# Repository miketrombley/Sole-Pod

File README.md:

# Sole Pod Control System

An ESP32-based firmware for controlling a smart pod system with motorized door and tray, LED lighting, and wireless connectivity.

## 🚀 Features

### Core Functionality
- **Motorized Door & Tray Control**: Automated opening/closing sequence with precise position control
- **Smart LED Lighting**: Full-color NeoPixel LED with adjustable brightness and color
- **Hall Sensor Feedback**: Precise position detection for door and tray states
- **Safety Systems**: Motor stall detection with automatic shutdown
- **Persistent Settings**: All configurations saved to flash memory

### Connectivity
- **Bluetooth Low Energy (BLE)**: Local device control via mobile app
- **WiFi Integration**: Network connectivity with credential management
- **AWS IoT Core**: Cloud connectivity for remote monitoring and control
- **MQTT Communication**: Real-time state updates and commands

### User Interface
- **Physical Buttons**: Manual door and LED control
- **Child Lock**: Safety feature to prevent accidental operation
- **Status Indicators**: Real-time feedback on device state

## 📋 Hardware Requirements

### Compatible Hardware
- **Control Board**: v1.4
- **LED Board**: v1.2  
- **Hall Sensor Board**: v1.0
- **Microcontroller**: ESP32

### Pin Configuration
```cpp
// Motor Control
#define DOOR_MOTOR 46          // Door motor control
#define DOOR_DIRECTION 3       // Door motor direction
#define TRAY_MOTOR 10          // Tray motor control  
#define TRAY_DIRECTION 11      // Tray motor direction

// Sensors
#define SW_DOOR_CLOSED 45      // Door closed sensor
#define SW_DOOR_OPENED 48      // Door opened sensor
#define SW_TRAY_CLOSED 35      // Tray closed sensor
#define SW_TRAY_OPENED 36      // Tray opened sensor

// User Interface
#define DOOR_BTN 47            // Door control button
#define LED_BTN 21             // LED control button
#define LED_DATA_PIN 14        // NeoPixel data pin

// Safety
#define VOLTAGE_PIN 9          // Motor current monitoring
```

## 🏗️ Architecture

### System States
The pod operates in 5 distinct states:
1. **CLOSED** (0): Door closed, tray closed
2. **DOOR_MIDWAY** (1): Door transitioning, tray closed  
3. **DOOR_OPEN** (2): Door open, tray closed
4. **TRAY_MIDWAY** (3): Door open, tray transitioning
5. **OPEN** (4): Door open, tray open

### Operation Sequence
**Opening**: CLOSED → DOOR_MIDWAY → DOOR_OPEN → TRAY_MIDWAY → OPEN
**Closing**: OPEN → TRAY_MIDWAY → DOOR_OPEN → DOOR_MIDWAY → CLOSED

## 📱 BLE Interface

### Service UUID
`7d840001-11eb-4c13-89f2-246b6e0b0000`

### Characteristics
| Function | UUID | Type | Range | Description |
|----------|------|------|-------|-------------|
| Door Status | `7d840002-...0001` | R/W | 0-1 | 0=Closed, 1=Open |
| Door Position | `7d840003-...0002` | R/W | 50,100 | Partial/Full open |
| LED Status | `7d840004-...0003` | R/W | 0-1 | 0=Off, 1=On |
| LED Brightness | `7d840005-...0004` | R/W | 0-100 | Brightness percentage |
| LED Color | `7d840006-...0005` | R/W | Hex | 6-digit hex color code |
| WiFi Credentials | `7d840007-...0006` | W | String | Format: `SSIDENDNETWORKPASSWORDENDPASSWORD` |
| WiFi Status | `7d840008-...0007` | R/N | String | Connection status |

## ☁️ AWS IoT Integration

### Device Shadow Topics
- **Publish**: `$aws/things/pod_1/shadow/update`
- **Subscribe**: `$aws/things/pod_1/shadow/update/accepted`

### Shadow Document Structure
```json
{
  "state": {
    "reported": {
      "is_open": true,
      "nightlight": false,
      "color": "FF0000",
      "nightlight_brightness": 75
    },
    "desired": {
      "is_open": false,
      "nightlight": true,
      "color": "0000FF",
      "nightlight_brightness": 50
    }
  }
}
```

## 🔧 Configuration

### AWS Configuration
Update `aws_config.h` with your AWS IoT settings:
```cpp
#define AWS_IOT_ENDPOINT "your-endpoint-ats.iot.region.amazonaws.com"
#define DEVICE_NAME "your_device_name"
```

Replace the certificate and key constants with your device-specific credentials.

### WiFi Configuration
Default credentials can be set in `main.cpp`:
```cpp
const char* defaultSSID = "your_network";
const char* defaultPassword = "your_password";
```

## 🛡️ Safety Features

### Motor Stall Detection
- **Threshold**: 0.2V (configurable in `VoltageReader.h`)
- **Sampling**: 50-sample average for noise reduction
- **Response**: Immediate motor shutdown and system lockout
- **Recovery**: Requires power cycle after stall detection

### Child Lock
- Prevents accidental button operation
- Configurable via software flag
- Applies to both door and LED controls

## 📊 Debug Output

Enable debug mode in `main.cpp`:
```cpp
#define DEBUG_MODE true
```

### Debug Information Includes:
- Current pod state and target
- Sensor readings (door/tray positions)
- LED status (state, brightness, color)
- WiFi connection status and signal strength
- Motor voltage readings
- Safety system status

## 🔄 State Persistence

The system automatically saves and restores:
- LED color and brightness settings
- Door position preference (50% or 100% open)
- LED on/off state
- Door open/closed status

Settings are stored in ESP32 flash memory using the Preferences library.

## 🚦 Status Codes

### Safety Status
- `0`: OK - Normal operation
- `1`: Motor stall detected
- `2`: Obstacle detected  
- `3`: Overcurrent condition
- `4`: System error

### WiFi Status
- "Connected" - Successfully connected
- "Disconnected" - Not connected
- "Connection failed" - Failed to connect
- "SSID not available" - Network not found

## 🛠️ Development

### Dependencies
- Arduino ESP32 Core
- WiFiClientSecure
- PubSubClient (MQTT)
- ArduinoJson
- Adafruit NeoPixel
- ESP32 BLE Arduino
- Preferences

### Building
1. Install ESP32 board package in Arduino IDE
2. Install required libraries
3. Configure AWS certificates in `aws_config.h`
4. Upload to ESP32 device

### Testing
- Use serial monitor at 115200 baud for debug output
- Test BLE connectivity with compatible mobile app
- Verify AWS IoT connection in AWS Console
- Test all physical controls and sensors

## 📝 License

TBD

## 🤝 Contributing

[Add contribution guidelines if applicable]

## 📞 Support

[Add support contact information]

---

**Hardware Compatibility**: Control Board v1.4, LED Board v1.2, Hall Sensor Board v1.0

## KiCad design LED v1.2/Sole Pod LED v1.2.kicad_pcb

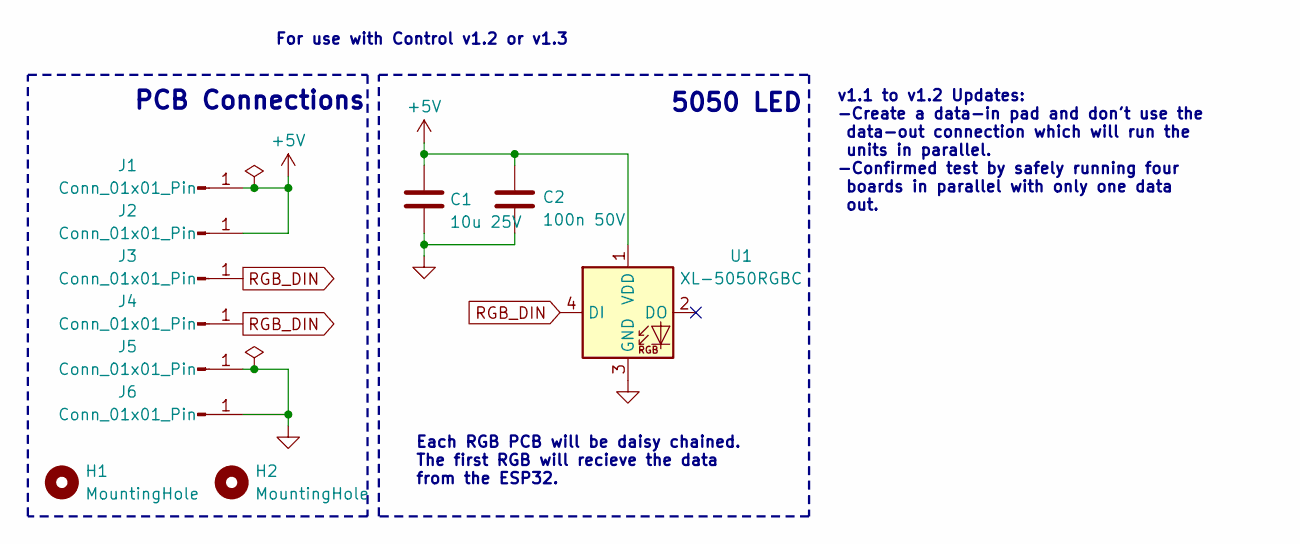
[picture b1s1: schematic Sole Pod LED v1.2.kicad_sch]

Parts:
C1: 10u 25V; C603; JLCPCB P/N C96446
C2: 100n 50V; C603; JLCPCB P/N C14663
H1, H2: MountingHole; MountingHole_2.5mm; JLCPCB P/N DNP
J1, J2, J3, J4, J5, J6: Conn_01x01_Pin; SolderWirePad_1x01_SMD_1x2mm; JLCPCB P/N DNP
U1: XL-5050RGBC; LED_Inolux_IN-PI554FCH_PLCC4_5.0x5.0mm_P3.2mm; JLCPCB P/N C2843785

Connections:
+5V: C1.1, C2.1, J1.1, J2.1, U1.1 (VDD)
GND: C1.2, C2.2, J5.1, J6.1, U1.3 (GND)
RGB_DIN: J3.1, J4.1, U1.4 (DI)

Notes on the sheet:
v1.1 to v1.2 Updates: -Create a data-in pad and don't use the data-out connection which will run the units in parallel. -Confirmed test by safely running four boards in parallel with only one data out.
PCB Connections
Each RGB PCB will be daisy chained. The first RGB will recieve the data from the ESP32.
5050 LED
For use with Control v1.2 or v1.3

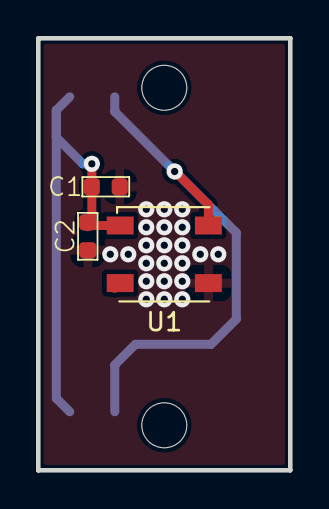
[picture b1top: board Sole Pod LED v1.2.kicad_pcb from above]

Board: 2 copper layers, 14.0 x 24.0 mm, 11 parts (0 on the bottom side), 3 nets.

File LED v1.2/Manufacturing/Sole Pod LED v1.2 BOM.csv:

Designator,Footprint,Quantity,Value,LCSC Part #
C1,C603,1,10u 25V,C96446
C2,C603,1,100n 50V,C14663
"J1, J2, J3, J4, J5, J6",SolderWirePad_1x01_SMD_1x2mm,6,Conn_01x01_Pin,DNP
U1,LED_Inolux_IN-PI554FCH_PLCC4_5.0x5.0mm_P3.2mm,1,XL-5050RGBC,C2843785

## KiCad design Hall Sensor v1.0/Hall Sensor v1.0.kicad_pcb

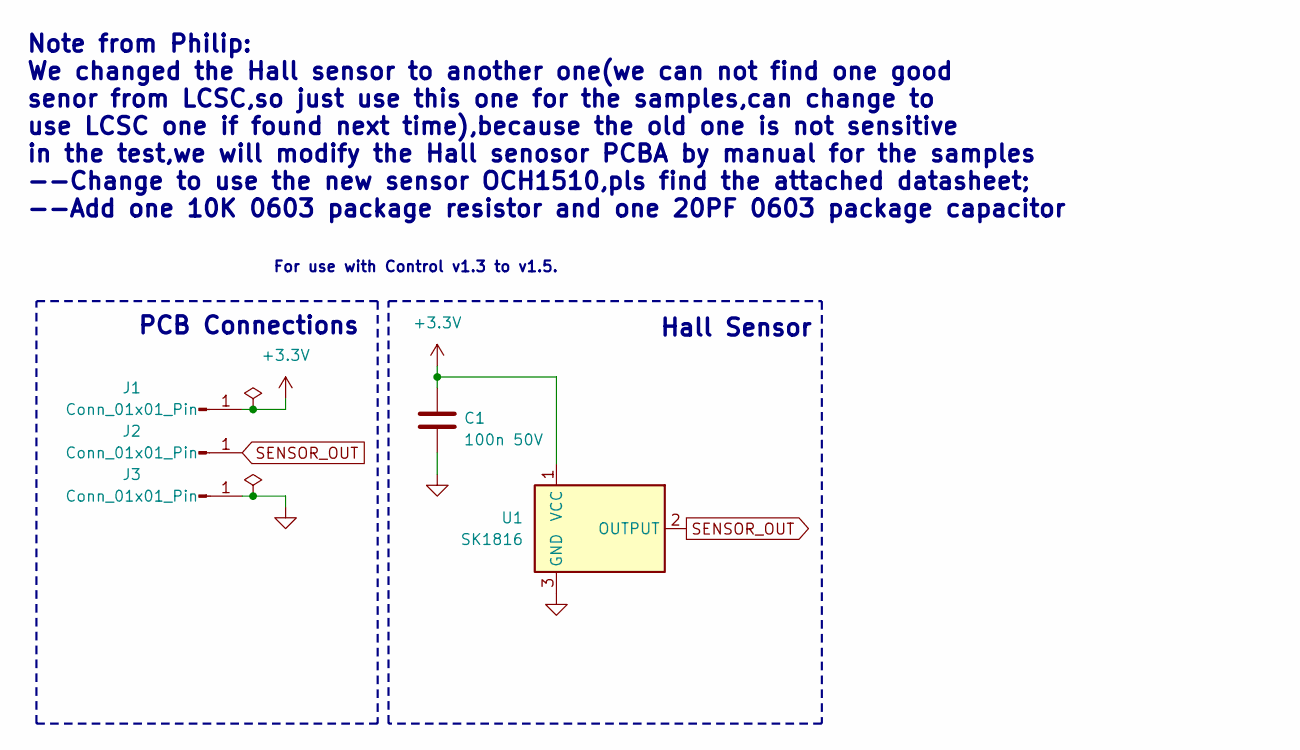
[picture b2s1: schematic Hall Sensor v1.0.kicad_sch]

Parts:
C1: 100n 50V; C603; JLCPCB P/N C14663
J1, J2, J3: Conn_01x01_Pin; SolderWirePad_1x01_SMD_1x2mm; JLCPCB P/N DNP
U1: SK1816; SOT-23; JLCPCB P/N C75517

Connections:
+3.3V: C1.1, J1.1, U1.1 (VCC)
GND: C1.2, J3.1, U1.3 (GND)
SENSOR_OUT: J2.1, U1.2 (OUTPUT)

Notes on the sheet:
PCB Connections
Hall Sensor
Note from Philip: We changed the Hall sensor to another one(we can not find one good senor from LCSC,so just use this one for the samples,can change to use LCSC one if found next time),because the old one is not sensitive in the test,we will modify the Hall senosor PCBA by manual for the samples --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
For use with Control v1.3 to v1.5.

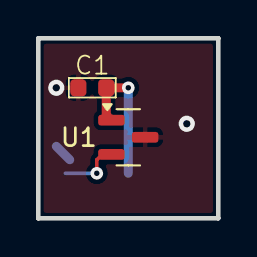
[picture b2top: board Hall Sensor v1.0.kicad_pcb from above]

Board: 2 copper layers, 10.0 x 10.0 mm, 5 parts (0 on the bottom side), 3 nets.

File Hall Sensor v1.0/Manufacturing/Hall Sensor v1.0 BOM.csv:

Designator,Footprint,Quantity,Value,LCSC Part #
C1,C603,1,100n 50V,C14663
"J1, J2, J3",SolderWirePad_1x01_SMD_1x2mm,3,Conn_01x01_Pin,DNP
U1,SOT-23,1,SK1816,C75517

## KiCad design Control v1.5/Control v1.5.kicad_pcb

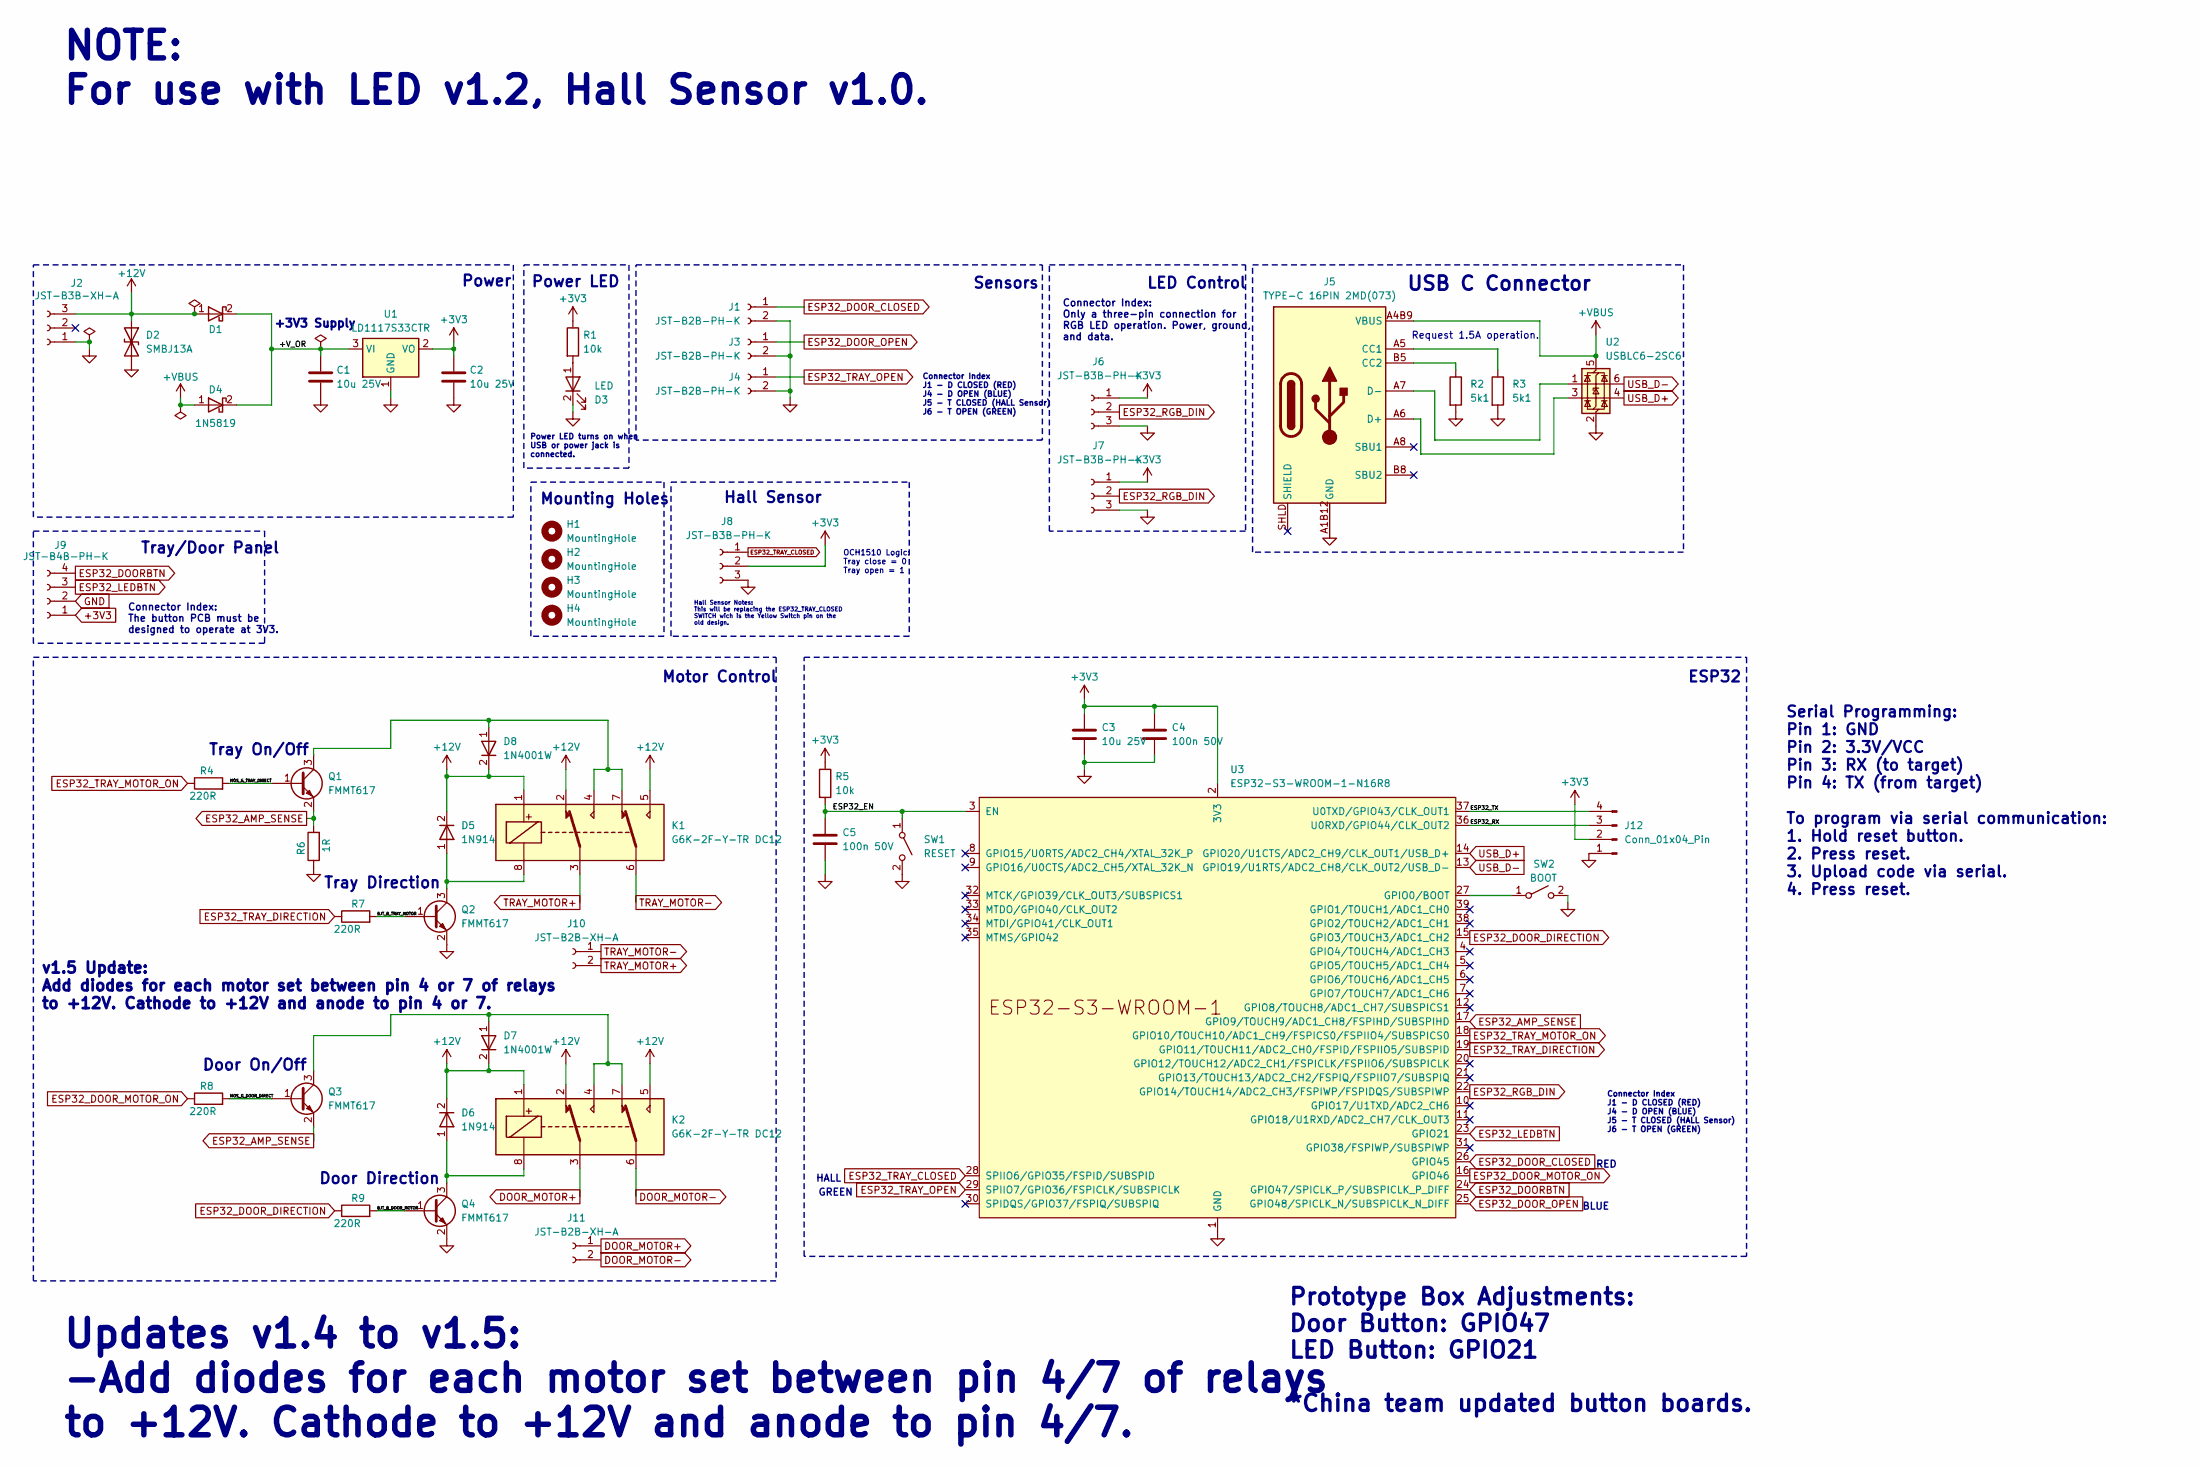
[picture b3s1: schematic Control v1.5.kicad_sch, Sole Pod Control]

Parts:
C1, C2, C3: 10u 25V; C603; LCSC Part # C96446
C4, C5: 100n 50V; C603; LCSC Part # C14663
D1, D4: 1N5819; D805; LCSC Part # C2927280
D2: SMBJ13A; D_SMB; LCSC Part # C152108
D3: LED; D603; LCSC Part # C497922
D5, D6: 1N914; D805; LCSC Part # C2128
D7, D8: 1N4001W; SOD-123; LCSC Part # C18199085
H1, H2, H3, H4: MountingHole; MountingHole_3mm; LCSC Part # DNP
J1, J3, J4: JST-B2B-PH-K; JST_PH_B2B-PH-K_1x02_P2.00mm_Vertical; LCSC Part # C131337
J2: JST-B3B-XH-A; JST_XH_B3B-XH-A_1x03_P2.50mm_Vertical; LCSC Part # C144394
J5: TYPE-C 16PIN 2MD(073); USB_C_TYPE-C_16PIN_2MD; LCSC Part # C2765186
J6, J7, J8: JST-B3B-PH-K; JST_PH_B3B-PH-K_1x03_P2.00mm_Vertical; LCSC Part # C131339
J9: JST-B4B-PH-K; JST_PH_B4B-PH-K_1x04_P2.00mm_Vertical; LCSC Part # C131334
J10, J11: JST-B2B-XH-A; JST_XH_B2B-XH-A_1x02_P2.50mm_Vertical; LCSC Part # C158012
J12: Conn_01x04_Pin; PinHeader_1x04_P2.54mm_Vertical; LCSC Part # C2691448
K1, K2: G6K-2F-Y-TR DC12; Relay_DPDT_Omron_G6K-2F-Y; LCSC Part # C397192
Q1, Q2, Q3, Q4: FMMT617; SOT-23-3; LCSC Part # C686650
R1, R5: 10k; R603; LCSC Part # C25804
R2, R3: 5k1; R603; LCSC Part # C25905
R4, R7, R8, R9: 220R; R603; LCSC Part # C22962
R6: 1R; R_1206_3216Metric; LCSC Part # C17928
SW1: RESET; SW_SPST_B3U-1000P; LCSC Part # C231329
SW2: BOOT; SW_SPST_B3U-1000P; LCSC Part # C231329
U1: LD1117S33CTR; SOT-223-3_TabPin2; LCSC Part # C35879
U2: USBLC6-2SC6; SOT-23-6; LCSC Part # C2827654
U3: ESP32-S3-WROOM-1-N16R8; ESP32-S3-WROOM-1; LCSC Part # C2913202

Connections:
+3V3: C2.1, C3.1, C4.1, J6.1, J7.1, J8.2, J9.1, J12.2, R1.1, R5.1, U1.2 (VO), U3.2 (3V3)
+12V: D1.1, D2.1 (A1), D5.2 (K), D6.2 (K), D7.2 (K), D8.2 (K), J2.3, K1.1, K1.2, K1.5, K2.1, K2.2, K2.5
+VBUS: D4.1, J5.A4B9 (VBUS), J5.B4A9 (VBUS), U2.5 (VBUS)
/+V_OR: C1.1, D1.2, D4.2, U1.3 (VI)
/BJT_B_DOOR_MOTOR: Q4.1 (B), R9.2
/BJT_B_TRAY_MOTOR: Q2.1 (B), R7.2
/ESP32_EN: C5.1, R5.2, SW1.1 (A), U3.3 (EN)
/ESP32_RX: J12.3, U3.36 (U0RXD/GPIO44/CLK_OUT2)
/ESP32_TX: J12.4, U3.37 (U0TXD/GPIO43/CLK_OUT1)
/MOS_G_DOOR_DIRECT: Q3.1 (B), R8.2
/MOS_G_TRAY_DIRECT: Q1.1 (B), R4.2
DOOR_MOTOR+: J11.1, K2.3
DOOR_MOTOR-: J11.2, K2.6
ESP32_AMP_SENSE: Q1.2 (E), Q3.2 (E), R6.2, U3.17 (GPIO9/TOUCH9/ADC1_CH8/FSPIHD/SUBSPIHD)
ESP32_DOORBTN: J9.4, U3.24 (GPIO47/SPICLK_P/SUBSPICLK_P_DIFF)
ESP32_DOOR_CLOSED: J1.1, U3.26 (GPIO45)
ESP32_DOOR_DIRECTION: R9.1, U3.15 (GPIO3/TOUCH3/ADC1_CH2)
ESP32_DOOR_MOTOR_ON: R8.1, U3.16 (GPIO46)
ESP32_DOOR_OPEN: J3.1, U3.25 (GPIO48/SPICLK_N/SUBSPICLK_N_DIFF)
ESP32_LEDBTN: J9.3, U3.23 (GPIO21)
ESP32_RGB_DIN: J6.2, J7.2, U3.22 (GPIO14/TOUCH14/ADC2_CH3/FSPIWP/FSPIDQS/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)
ESP32_TRAY_CLOSED: J8.1, U3.28 (SPIIO6/GPIO35/FSPID/SUBSPID)
ESP32_TRAY_DIRECTION: R7.1, U3.19 (GPIO11/TOUCH11/ADC2_CH0/FSPID/FSPIIO5/S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)
ESP32_TRAY_MOTOR_ON: R4.1, U3.18 (GPIO10/TOUCH10/ADC1_CH9/FSPICS0/FSPIIO4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)
ESP32_TRAY_OPEN: J4.1, U3.29 (SPIIO7/GPIO36/FSPICLK/SUBSPICLK)
GND: C1.2, C2.2, C3.2, C4.2, C5.2, D2.2 (A2), D3.2 (K), J1.2, J2.1, J3.2, J4.2, J5.A1B12 (GND), J5.B1A12 (GND), J6.3, J7.3, J8.3, J9.2, J12.1, Q2.2 (E), Q4.2 (E), R2.2, R3.2, R6.1, SW1.2 (B), SW2.2 (B), U1.1 (GND), U2.2 (GND), U3.1 (GND), U3.40 (GND), U3.41 (GND)
unnamed: D3.1 (A), R1.2
unnamed: D5.1 (A), K1.8, Q2.3 (C)
unnamed: D6.1 (A), K2.8, Q4.3 (C)
unnamed: D7.1 (A), K2.4, K2.7, Q3.3 (C)
unnamed: D8.1 (A), K1.4, K1.7, Q1.3 (C)
unnamed: J5.A5 (CC1), R3.1
unnamed: J5.B5 (CC2), R2.1
unnamed: J5.A6 (D+), J5.B6 (D+), U2.3 (I/O2)
unnamed: J5.A7 (D-), J5.B7 (D-), U2.1 (I/O1)
unnamed: SW2.1 (A), U3.27 (GPIO0/BOOT)
TRAY_MOTOR+: J10.2, K1.3
TRAY_MOTOR-: J10.1, K1.6
USB_D+: U2.4 (I/O2), U3.14 (GPIO20/U1CTS/ADC2_CH9/CLK_OUT1/USB_D+)
USB_D-: U2.6 (I/O1), U3.13 (GPIO19/U1RTS/ADC2_CH8/CLK_OUT2/USB_D-)

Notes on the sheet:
Tray On/Off
ESP32
HALL
NOTE: For use with LED v1.2, Hall Sensor v1.0.
USB C Connector
Connector Index: Only a three-pin connection for RGB LED operation. Power, ground, and data.
BLUE
Mounting Holes
Tray Direction
v1.5 Update: Add diodes for each motor set between pin 4 or 7 of relays to +12V. Cathode to +12V and anode to pin 4 or 7.
Connector Index J1 - D CLOSED (RED) J4 - D OPEN (BLUE) J5 - T CLOSED (HALL Sensor) J6 - T OPEN (GREEN)
Updates v1.4 to v1.5: -Add diodes for each motor set between pin 4/7 of relays to +12V. Cathode to +12V and anode to pin 4/7.
Connector Index: The button PCB must be designed to operate at 3V3.
Motor Control
Request 1.5A operation.
GREEN
OCH1510 Logic: Tray close = 0 Tray open = 1
Power LED
Sensors
Door Direction
Serial Programming: Pin 1: GND Pin 2: 3.3V/VCC Pin 3: RX (to target) Pin 4: TX (from target) To program via serial communication: 1. Hold reset button. 2. Press reset. 3. Upload code via serial. 4. Press reset.
Hall Sensor
Tray/Door Panel
Power LED turns on when USB or power jack is connected.
Hall Sensor Notes: This will be replacing the ESP32_TRAY_CLOSED SWITCH wich is the Yellow Switch pin on the old design.
Door On/Off
+3V3 Supply
Power
RED
Prototype Box Adjustments: Door Button: GPIO47 LED Button: GPIO21 *China team updated button boards.
LED Control

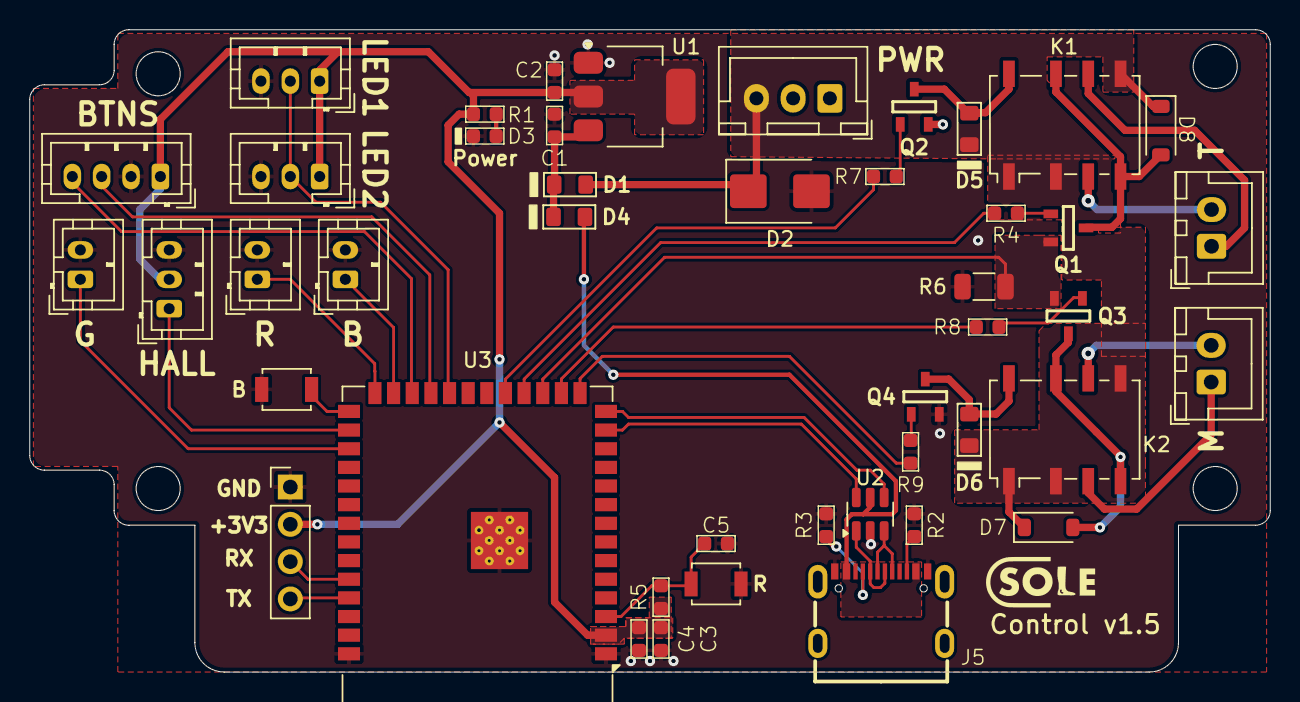
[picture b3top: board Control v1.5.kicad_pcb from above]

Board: 2 copper layers, 84.5 x 43.8 mm, 49 parts (0 on the bottom side), 40 nets.

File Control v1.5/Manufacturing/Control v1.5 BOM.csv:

Designator,Footprint,Quantity,Value,LCSC Part #
"C1, C2, C3",C603,3,10u 25V,C96446
"C4, C5",C603,2,100n 50V,C14663
"D1, D4",D805,2,1N5819,C2927280
D2,D_SMB,1,SMBJ13A,C152108
D3,D603,1,LED,C497922
"D5, D6",D805,2,1N914,C2128
"D7, D8",SOD-123,2,1N4001W,C18199085
"J1, J3, J4",JST_PH_B2B-PH-K_1x02_P2.00mm_Vertical,3,JST-B2B-PH-K,C131337
"J10, J11",JST_XH_B2B-XH-A_1x02_P2.50mm_Vertical,2,JST-B2B-XH-A,C158012
J12,PinHeader_1x04_P2.54mm_Vertical,1,Conn_01x04_Pin,C2691448
J2,JST_XH_B3B-XH-A_1x03_P2.50mm_Vertical,1,JST-B3B-XH-A,C144394
J5,USB_C_TYPE-C_16PIN_2MD,1, TYPE-C 16PIN 2MD(073),C2765186
"J6, J7, J8",JST_PH_B3B-PH-K_1x03_P2.00mm_Vertical,3,JST-B3B-PH-K,C131339
J9,JST_PH_B4B-PH-K_1x04_P2.00mm_Vertical,1,JST-B4B-PH-K,C131334
"K1, K2",Relay_DPDT_Omron_G6K-2F-Y,2,G6K-2F-Y-TR DC12,C397192
"Q1, Q2, Q3, Q4",SOT-23-3,4,FMMT617,C686650
"R1, R5",R603,2,10k,C25804
"R2, R3",R603,2,5k1,C25905
"R4, R7, R8, R9",R603,4,220R,C22962
R6,1206,1,1R,C17928
SW1,SW_SPST_B3U-1000P,1,RESET,C231329
SW2,SW_SPST_B3U-1000P,1,BOOT,C231329
U1,SOT-223-3_TabPin2,1,LD1117S33CTR,C35879
U2,SOT-23-6,1,USBLC6-2SC6,C2827654
U3,ESP32-S3-WROOM-1,1,ESP32-S3-WROOM-1-N16R8 ,C2913202

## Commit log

2025-05-01 Initial commit.
2025-05-01 Default brightness set to max.
2025-05-01 Kept safety code but commented out for better performance.
2025-05-01 BLE Revision - Door Open
2025-05-01 BLE Revision - LED On
2025-05-01 BLE Revision - LED Brightness
2025-05-01 BLE Revision - Door Open Half/Full Capability
2025-05-01 BLE Revision - LED Color
2025-05-01 Load/Save LED Status/Brightness/Color and Door Position.
2025-05-01 Updated motor direction to work with Control v1.4 assemblies.
2025-05-01 Ability to load/save door status.
2025-05-02 WiFi management capabilites added (Hardcode Network).
2025-05-02 BLE Revision - WiFi Connect
2025-05-02 Update BLE/WiFi connection relability.
2025-05-02 Minor update in BLE callbacks.
2025-05-27 Allow wifi to connect
2025-05-29 Updated LED library for use with NEO pixel.
2025-06-04 Add BLE child lock capabilities.
2025-06-04 A more reliable and robust advertising scheme.
2025-06-04 Fixed the issue with passing a 0 in LED brightness.
2025-06-11 Updated LED control to work with new BLE code.
2025-06-11 Updated LED to use FastLED.
2025-06-11 Added README.
2025-06-11 Added JSON characteristic.
2025-06-12 Added JSON and KiCAD files.
2025-08-19 feat: ble and wifi handle
2025-08-19 chore: update logic for childlock
